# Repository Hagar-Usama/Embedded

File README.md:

# Embedded 📟

![Intel-8085][1] ![Embedded-PCB][2]  ![kicad][4] ![Corona-Stuck][3]
![license-GPL3][5]

[GPL3 License](https://www.gnu.org/licenses/gpl-3.0.en.html "GPL3")

[1]: https://img.shields.io/:Intel-8085-default.svg?style=round-square
[2]: https://img.shields.io/:Embedded-PCB-darkgreen.svg?style=round-square
[3]: https://img.shields.io/:Covid_19-Stuck-maroon.svg?style=round-square
[4]: https://img.shields.io/:Ki-CAD-darkblue.svg?style=round-square
[5]: https://img.shields.io/:license-GPL3-yellow.svg?style=round-square

---

## Table of Contents
* [Introduction][10]

<!--
* [Technologies][11]
* [Launch][12]
* [Restrictions][13]
-->

* [Images][14]

<!--
* [Contributing][15]
-->

* [To-do List][16]

<!--
* [Bugs][17]
-->

[10]: #introduction

[11]: #technologies

[12]: #launch

[13]: #-restrictions

[14]: #images

[15]: #contributing

[16]: #to-do-list

[17]: #bugs-

[18]: #license

---

## Introduction

Fed up with breadboards 😤? OK! Enough breadboards. We can wire breadboards neatly 😎. Let's make a PCB! See motherboards? We will make our PCB modular, based on modules.

Hey, we do this in programming. Yup, ideas are applicable everywhere! Yet, we cannot keep fabrication and testing due to Covid-19  😷.

---
<!--

## Technologies

* Fixed-format and free-format

* Regex is used for validation

* Graphical User Interface

---
-->

<!--## Launch  > TBD

<!-- ## 🚫 **Restrictions** -->

## Images

Module 1

<!--
## Contributing
 See 👉  [CONTRIBUTING.md][27] -->

[27]:https://github.com/Hagar-Usama/Embedded/blob/master/CONTRIBUTING.md

---

## To-do List
* [x] build a neat README
* [x] upload scheme and PCB layout
* [ ] upload testing codes

<!-- ## Bugs 🐞-->

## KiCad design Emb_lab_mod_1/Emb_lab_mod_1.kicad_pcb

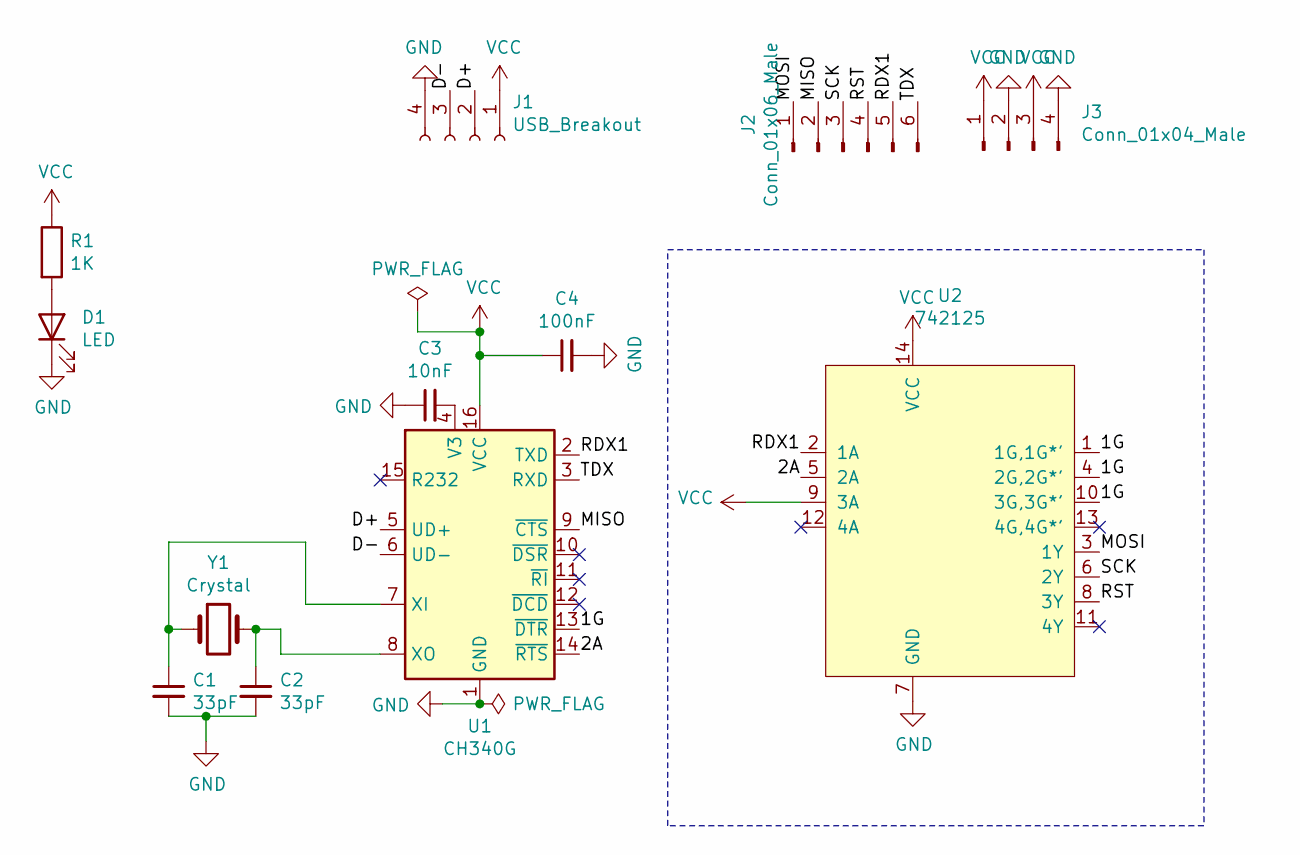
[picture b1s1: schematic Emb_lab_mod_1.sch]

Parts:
C1, C2: 33pF; C_Disc_D6.0mm_W4.4mm_P5.00mm
C3: 10nF; C_Rect_L7.0mm_W2.0mm_P5.00mm
C4: 100nF; C_Rect_L7.0mm_W2.0mm_P5.00mm
D1: LED; LED_D3.0mm
J1: USB_Breakout; PinSocket_1x04_P2.54mm_Vertical
J2: Conn_01x06_Male; PinHeader_1x06_P2.54mm_Vertical
J3: Conn_01x04_Male; PinHeader_1x04_P2.54mm_Vertical
R1: 1K; R_Axial_DIN0204_L3.6mm_D1.6mm_P7.62mm_Horizontal
U1: CH340G; CH340_With_Adapter
U2: 742125; 74125
Y1: Crystal; Crystal_HC18-U_Vertical

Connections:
/1G: U1.13 (~DTR), U2.1 (1G,1G*'), U2.4 (2G,2G*'), U2.10 (3G,3G*')
/2A: U1.14 (~RTS), U2.5 (2A)
/D+: J1.2, U1.5 (UD+)
/D-: J1.3, U1.6 (UD-)
/MISO: J2.2, U1.9 (~CTS)
/MOSI: J2.1, U2.3 (1Y)
/RDX1: J2.5, U1.2 (TXD), U2.2 (1A)
/RST: J2.4, U2.8 (3Y)
/SCK: J2.3, U2.6 (2Y)
/TDX: J2.6, U1.3 (RXD)
GND: C1.2, C2.2, C3.1, C4.2, D1.1 (K), J1.4, J3.2, J3.4, U1.1 (GND), U2.7 (GND)
unnamed: C1.1, U1.7 (XI), Y1.1
unnamed: C2.1, U1.8 (XO), Y1.2
unnamed: C3.2, U1.4 (V3)
unnamed: D1.2 (A), R1.2
VCC: C4.1, J1.1, J3.1, J3.3, R1.1, U1.16 (VCC), U2.9 (3A), U2.14 (VCC)

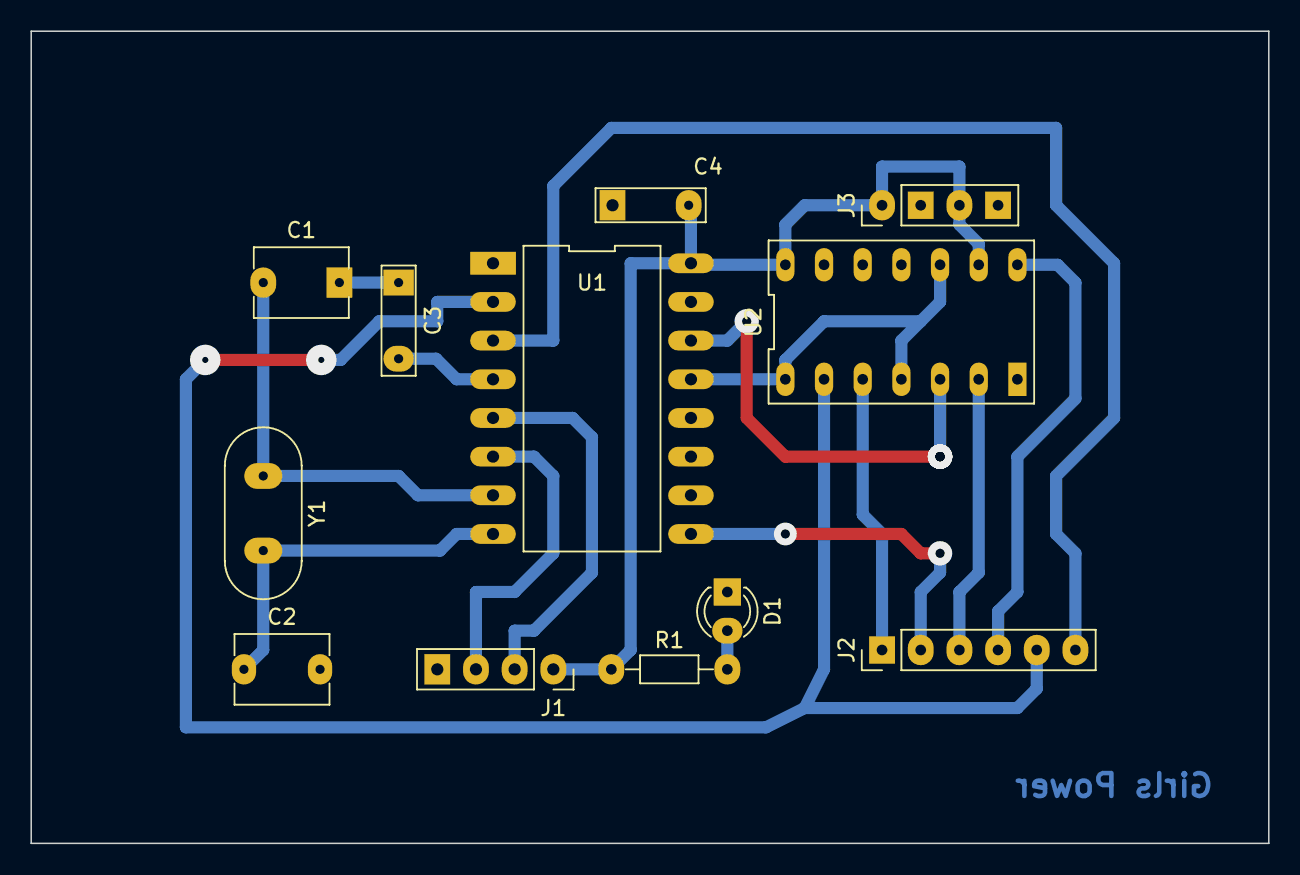
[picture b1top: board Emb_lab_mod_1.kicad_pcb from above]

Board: 2 copper layers, 81.3 x 53.3 mm, 12 parts (0 on the bottom side), 16 nets.

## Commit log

2020-04-12 add images
2020-04-12 add images to readme
2021-08-09 add kicad modul 1
2021-08-09 fix typo
